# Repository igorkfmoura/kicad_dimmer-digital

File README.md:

# Digital Dimmer with ATtiny13

## Description

A simple digital dimmer using a cheap 8-bits AVR ATtiny13, made for educational purposes.

It have been designed to be controlled by a potentiometer (externally connected via 2.54mm headers) or a analog or PWM 0-5V signal.

## Speed Input

The speed input signal source can be either from a potenciometer or a external 0-5V signal.

The source is selected by the SWITCH_SPEED (externally connected via 2.54mm headers).

The 0-5V signal is filted by a low-pass filter defined by R1 and C1.

## Disclaimers

This circuit:

* handles AC voltage and may be dangerous;

* have not been tested yet;

* does not include fuse.

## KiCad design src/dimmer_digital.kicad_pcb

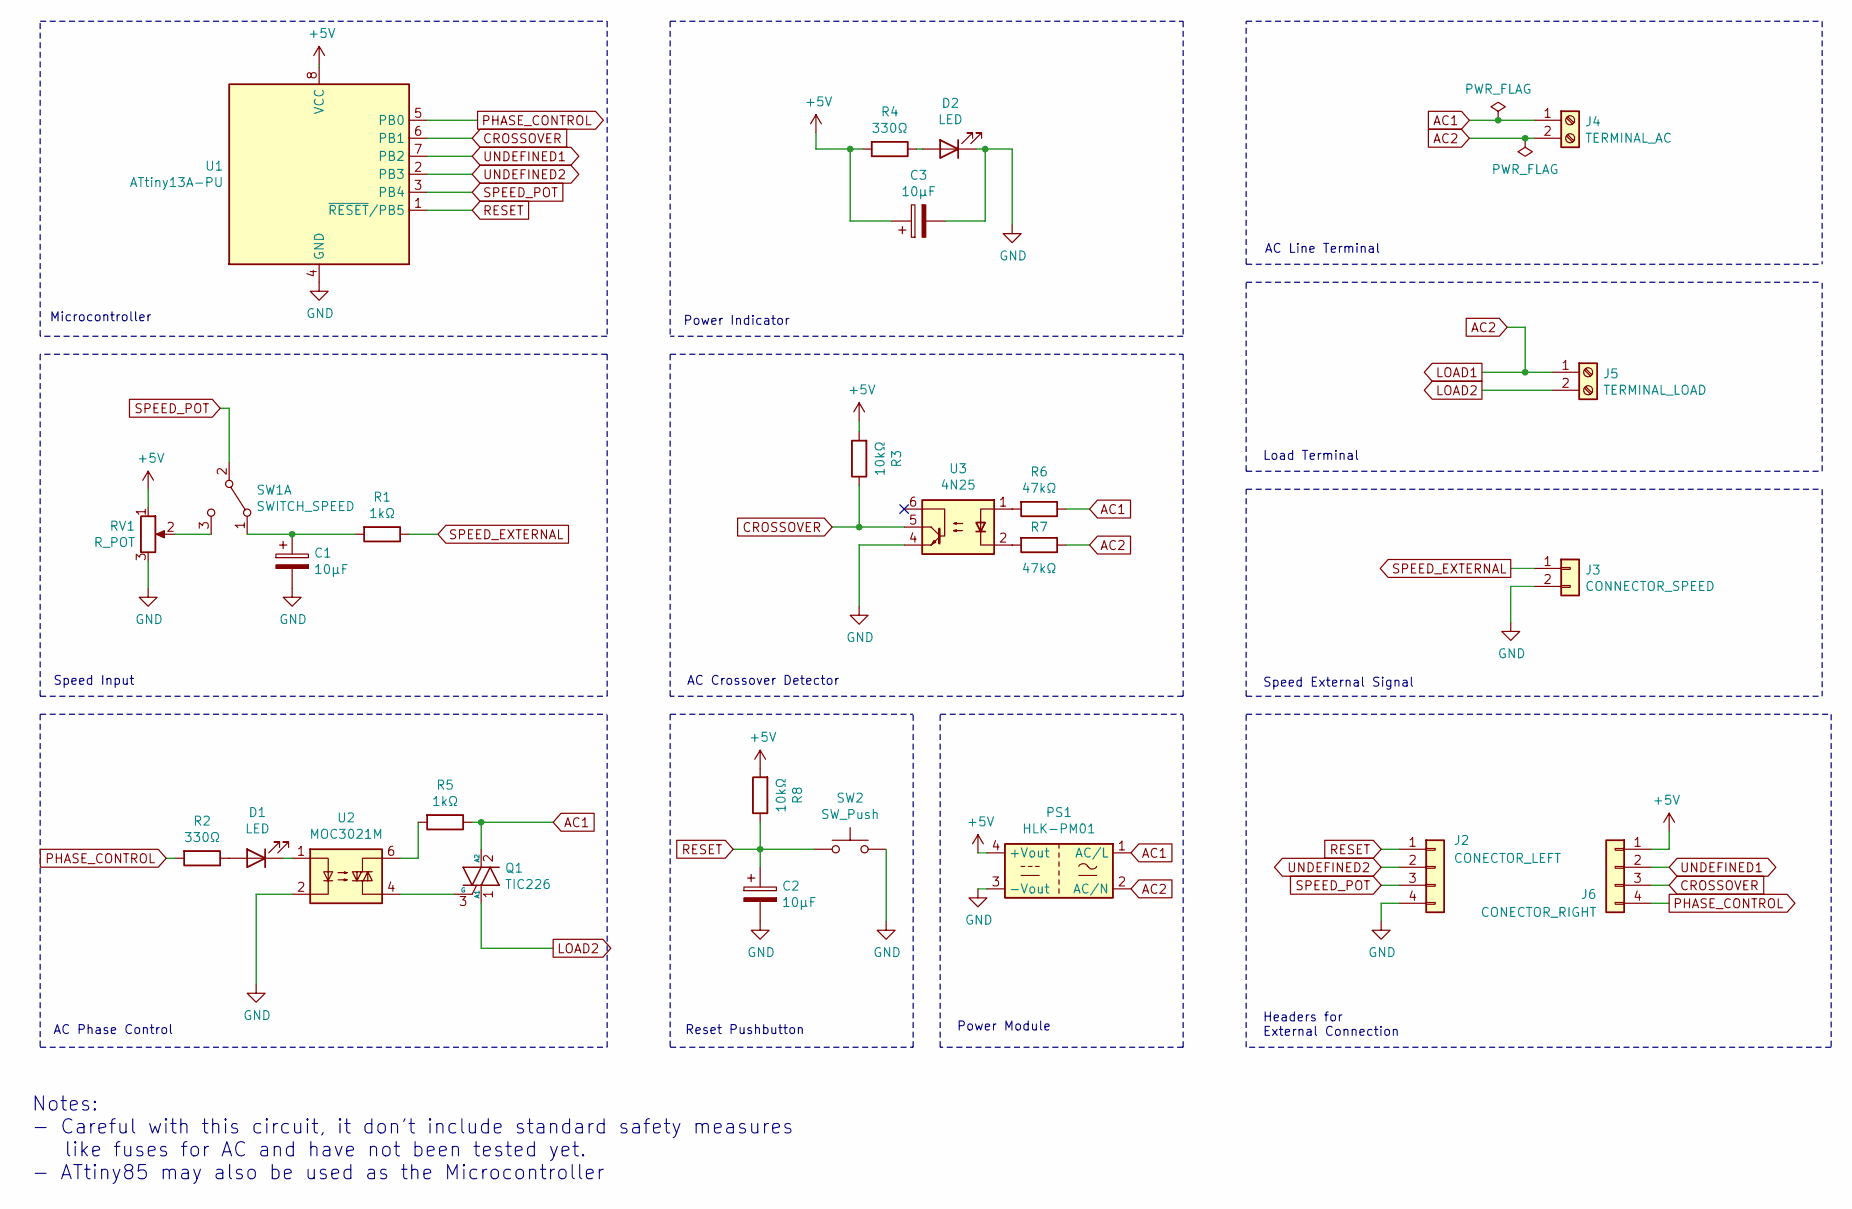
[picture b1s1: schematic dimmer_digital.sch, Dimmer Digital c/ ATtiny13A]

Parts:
C1, C2, C3: 10µF; CP_Radial_D5.0mm_P2.50mm
D1, D2: LED; LED_D3.0mm
J2: CONECTOR_LEFT; PinHeader_1x04_P2.54mm_Vertical
J3: CONNECTOR_SPEED; PinHeader_1x02_P2.54mm_Vertical
J4: TERMINAL_AC; TerminalBlock_bornier-2_P5.08mm
J5: TERMINAL_LOAD; TerminalBlock_bornier-2_P5.08mm
J6: CONECTOR_RIGHT; PinHeader_1x04_P2.54mm_Vertical
PS1: HLK-PM01; Converter_ACDC_HiLink_HLK-PMxx
Q1: TIC226; TO-220-3_Vertical
R1, R5: 1kΩ; R_Axial_DIN0207_L6.3mm_D2.5mm_P7.62mm_Horizontal
R2, R4: 330Ω; R_Axial_DIN0207_L6.3mm_D2.5mm_P7.62mm_Horizontal
R3, R8: 10kΩ; R_Axial_DIN0207_L6.3mm_D2.5mm_P7.62mm_Horizontal
R6, R7: 47kΩ; R_Axial_DIN0207_L6.3mm_D2.5mm_P7.62mm_Horizontal
RV1: R_POT; PinHeader_1x03_P2.54mm_Vertical
SW1: SWITCH_SPEED; PinHeader_1x03_P2.54mm_Vertical
SW2: SW_Push; SW_PUSH_6mm
U1: ATtiny13A-PU; DIP-8_W7.62mm_Socket
U2: MOC3021M; DIP-6_W7.62mm_Socket
U3: 4N25; DIP-6_W7.62mm_Socket

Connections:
+5V: C3.1, J6.1, PS1.4 (+Vout), R3.2, R4.2, R8.2, RV1.1, U1.8 (VCC)
AC1: J4.1, PS1.1 (AC/L), Q1.2 (A2), R5.1, R6.1
AC2: J4.2, J5.1, PS1.2 (AC/N), R7.1
CROSSOVER: J6.3, R3.1, U1.6 (PB1), U3.5
GND: C1.2, C2.2, C3.2, D2.1 (K), J2.4, J3.2, PS1.3 (-Vout), RV1.3, SW2.2, U1.4 (GND), U2.2, U3.4
LOAD2: J5.2, Q1.1 (A1)
unnamed: C1.1, R1.2, SW1.1 (A)
unnamed: D1.1 (K), U2.1
unnamed: D1.2 (A), R2.1
unnamed: D2.2 (A), R4.1
unnamed: Q1.3 (G), U2.4
unnamed: R5.2, U2.6
unnamed: R6.2, U3.1
unnamed: R7.2, U3.2
unnamed: RV1.2, SW1.3 (C)
PHASE_CONTROL: J6.4, R2.2, U1.5 (PB0)
RESET: C2.1, J2.1, R8.1, SW2.1, U1.1 (~RESET~/PB5)
SPEED_EXTERNAL: J3.1, R1.1
SPEED_POT: J2.3, SW1.2 (B), U1.3 (PB4)
UNDEFINED1: J6.2, U1.7 (PB2)
UNDEFINED2: J2.2, U1.2 (PB3)

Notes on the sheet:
Power Indicator
Power Module
AC Crossover Detector
Speed Input
Speed External Signal
AC Phase Control
Load Terminal
Headers for External Connection
AC Line Terminal
Reset Pushbutton
Microcontroller
Notes: - Careful with this circuit, it don't include standard safety measures like fuses for AC and have not been tested yet. - ATtiny85 may also be used as the Microcontroller

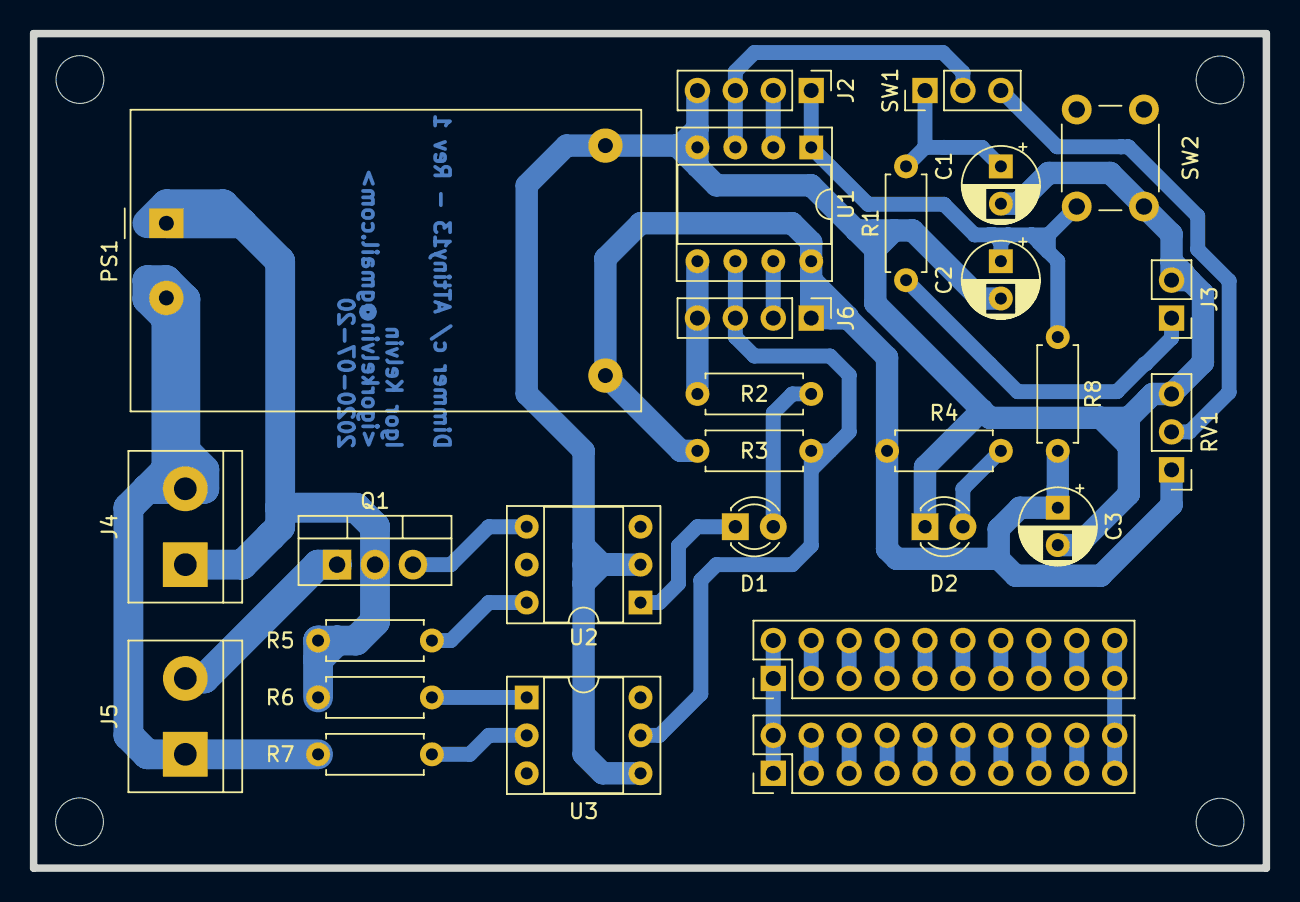
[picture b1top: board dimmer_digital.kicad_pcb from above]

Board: 2 copper layers, 82.5 x 55.9 mm, 26 parts (0 on the bottom side), 21 nets.

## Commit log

2020-03-13 Placed components
2020-03-14 wiring up
2020-07-11 Updated components & wiring
2020-07-11 Footprints
2020-07-11 Update page, added headers for attiny13a, started pcb layout
2020-07-11 positioning AC side
2020-07-11 wiring AC side
2020-07-11 wiring complete
2020-07-11 Finished Rev0
2020-07-12 Visual update on the schematic
2020-07-13 add screw mount holes
2020-07-20 Project files rearrangement
2020-07-20 License and readme changes
2020-07-20 Readme and folder rename
2020-07-20 Added custom libraries references to local
2020-07-21 Added pullup to reset pin
2020-07-21 Footprint Rev1
